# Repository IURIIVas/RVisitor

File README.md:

# RVisitor

Automated robot motion control module

## Description

The module allows to assign the control functions of a wheeled robot to a separate functional unit, reducing the requirements for robot software.   

### Application area
The module provides control of DC motors taking into account information from connected sensors. The module can be used for:
* studying the basic robotic algorithms for controlling the movement of wheeled robots
* research and development of robotic platforms

### Features

* setting and maintaining speed and direction of movement
* identification of obstacles and lack of surface
* wheel odometry
* high current level detection
* configuration save

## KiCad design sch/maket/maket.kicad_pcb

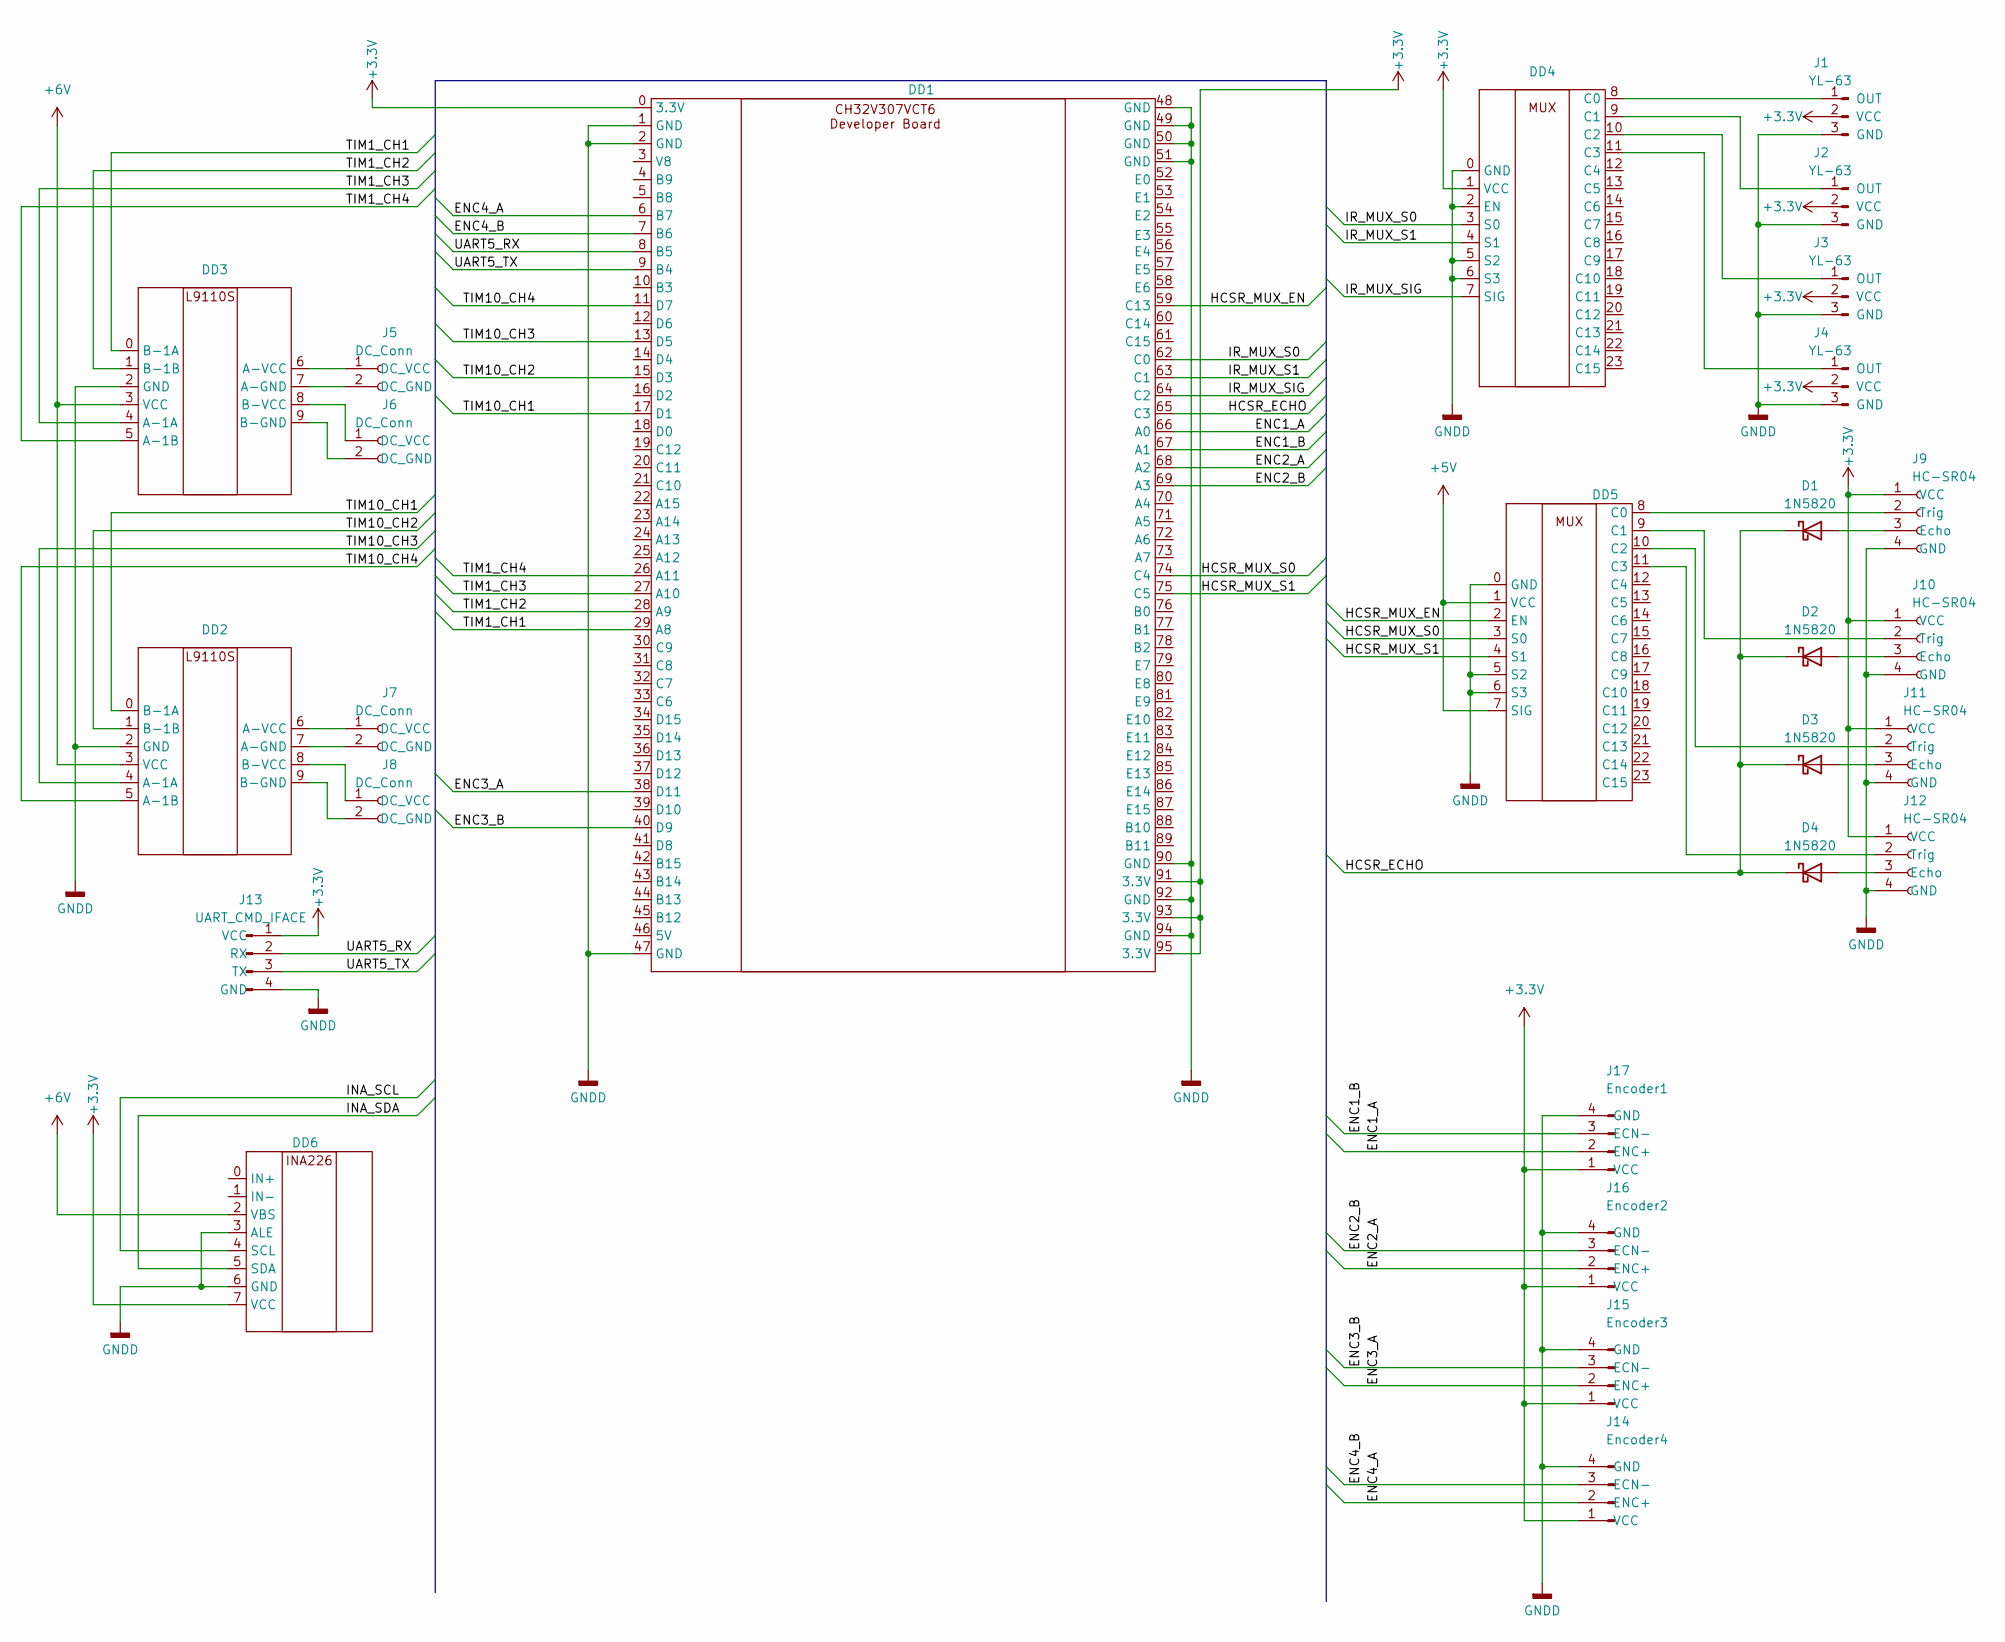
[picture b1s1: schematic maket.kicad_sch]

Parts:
D1, D2, D3, D4: 1N5820; D_DO-201AD_P15.24mm_Horizontal
DD1: CH32V307VCT6 dev board
DD2, DD3: L9110S
DD4, DD5: CD74HC4067_GOOD
DD6: INA226
J1, J2, J3, J4: YL-63; PinHeader_1x03_P2.54mm_Vertical
J5, J6, J7, J8: DC_Conn; JST_PH_S2B-PH-K_1x02_P2.00mm_Horizontal
J9, J10, J11, J12: HC-SR04; PinSocket_1x04_P2.54mm_Vertical
J13: UART_CMD_IFACE; PinSocket_1x04_P2.54mm_Vertical
J14: Encoder4; JST_PH_S4B-PH-K_1x04_P2.00mm_Horizontal
J15: Encoder3; JST_PH_S4B-PH-K_1x04_P2.00mm_Horizontal
J16: Encoder2; JST_PH_S4B-PH-K_1x04_P2.00mm_Horizontal
J17: Encoder1; JST_PH_S4B-PH-K_1x04_P2.00mm_Horizontal

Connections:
+3.3V: DD1.0 (3.3V), DD1.74 (C4), DD1.75 (C5), DD1.91 (3.3V), DD1.93 (3.3V), DD1.95 (3.3V), DD4.1 (VCC), DD5.3 (S0), DD5.4 (S1), DD6.7 (VCC), J1.2 (VCC), J2.2 (VCC), J3.2 (VCC), J4.2 (VCC), J9.1 (VCC), J10.1 (VCC), J11.1 (VCC), J12.1 (VCC), J13.1 (VCC), J14.1 (VCC), J15.1 (VCC), J16.1 (VCC), J17.1 (VCC)
+5V: DD5.1 (VCC), DD5.7 (SIG)
+6V: DD2.3 (VCC), DD3.3 (VCC), DD6.2 (VBS)
/ENC1_A: DD1.66 (A0), J17.2 (ENC+)
/ENC1_B: DD1.67 (A1), J17.3 (ECN-)
/ENC2_A: DD1.68 (A2), J16.2 (ENC+)
/ENC2_B: DD1.69 (A3), J16.3 (ECN-)
/ENC3_A: DD1.38 (D11), J15.2 (ENC+)
/ENC3_B: DD1.40 (D9), J15.3 (ECN-)
/ENC4_A: DD1.6 (B7), J14.2 (ENC+)
/ENC4_B: DD1.7 (B6), J14.3 (ECN-)
/HCSR_ECHO: D1.1 (K), D2.1 (K), D3.1 (K), D4.1 (K), DD1.65 (C3)
/HCSR_MUX_EN: DD1.59 (C13), DD5.2 (EN)
/INA_SCL: DD6.4 (SCL)
/INA_SDA: DD6.5 (SDA)
/IR_MUX_S0: DD1.62 (C0), DD4.3 (S0)
/IR_MUX_S1: DD1.63 (C1), DD4.4 (S1)
/IR_MUX_SIG: DD1.64 (C2), DD4.7 (SIG)
/TIM1_CH1: DD1.29 (A8), DD3.0 (B-1A)
/TIM1_CH2: DD1.28 (A9), DD3.1 (B-1B)
/TIM1_CH3: DD1.27 (A10), DD3.4 (A-1A)
/TIM1_CH4: DD1.26 (A11), DD3.5 (A-1B)
/TIM10_CH1: DD1.17 (D1), DD2.0 (B-1A)
/TIM10_CH2: DD1.15 (D3), DD2.1 (B-1B)
/TIM10_CH3: DD1.13 (D5), DD2.4 (A-1A)
/TIM10_CH4: DD1.11 (D7), DD2.5 (A-1B)
/UART5_RX: DD1.8 (B5), J13.2 (RX)
/UART5_TX: DD1.9 (B4), J13.3 (TX)
GNDD: DD1.1 (GND), DD1.2 (GND), DD1.47 (GND), DD1.48 (GND), DD1.49 (GND), DD1.50 (GND), DD1.51 (GND), DD1.90 (GND), DD1.92 (GND), DD1.94 (GND), DD2.2 (GND), DD3.2 (GND), DD4.0 (GND), DD4.2 (EN), DD4.5 (S2), DD4.6 (S3), DD5.0 (GND), DD5.5 (S2), DD5.6 (S3), DD6.3 (ALE), DD6.6 (GND), J1.3 (GND), J2.3 (GND), J3.3 (GND), J4.3 (GND), J9.4 (GND), J10.4 (GND), J11.4 (GND), J12.4 (GND), J13.4 (GND), J14.4 (GND), J15.4 (GND), J16.4 (GND), J17.4 (GND)
unnamed: D1.2 (A), J9.3 (Echo)
unnamed: D2.2 (A), J10.3 (Echo)
unnamed: D3.2 (A), J11.3 (Echo)
unnamed: D4.2 (A), J12.3 (Echo)
unnamed: DD2.7 (A-GND), J7.2 (DC_GND)
unnamed: DD2.6 (A-VCC), J7.1 (DC_VCC)
unnamed: DD2.9 (B-GND), J8.2 (DC_GND)
unnamed: DD2.8 (B-VCC), J8.1 (DC_VCC)
unnamed: DD3.7 (A-GND), J5.2 (DC_GND)
unnamed: DD3.6 (A-VCC), J5.1 (DC_VCC)
unnamed: DD3.9 (B-GND), J6.2 (DC_GND)
unnamed: DD3.8 (B-VCC), J6.1 (DC_VCC)
unnamed: DD4.8 (C0), J1.1 (OUT)
unnamed: DD4.9 (C1), J2.1 (OUT)
unnamed: DD4.10 (C2), J3.1 (OUT)
unnamed: DD4.11 (C3), J4.1 (OUT)
unnamed: DD5.8 (C0), J9.2 (Trig)
unnamed: DD5.9 (C1), J10.2 (Trig)
unnamed: DD5.10 (C2), J11.2 (Trig)
unnamed: DD5.11 (C3), J12.2 (Trig)

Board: 2 copper layers, 27 parts (0 on the bottom side), 47 nets, no tracks yet.

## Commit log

2023-10-18 Initial commit. Blink LEDs Function
2023-10-21 Command Interface on USART2. print Hello World and unknown command added to command interface.
2023-10-22 IR sensor HW-201 init.
2023-11-09 dc motor 0 driver. change direction with cmd interface
2023-11-10 Speed change function added. lib/m_string - added str to int convertion.
2023-11-26 Change USART2 pins to GPIOD. GPIO init function of hw-201 fixed
2023-11-28 HC_SR04 capture started. Added Trig pin functionality with timer and gpio.
2023-11-30 trig pin enable function fixed, 9 timer used to count 10 microseconds
2023-12-01 echo from hc-sr04 get. distance
2023-12-09 hard fault issue
2023-12-11 pid controller develop started.
    - change vTaskDelay from ticks to ms
    - delete blink_led_task
    - convert string to double function added
    - pow function added
2023-12-13 cmd interface sends data in 2 seconds dc_control only by pid, in cmd iface only speed requiered all settings goes to struct tim8 changed to tim10 tim3 changed to tim9 usart2 changed to uart5 defined 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
2023-12-17 function string to double changed tim for dc control changed, from tim8 to tim10 tim3 changes for tim9 hc_sr04 now not working, because of no timer
2023-12-17 working pid
2023-12-17 odometry task. calculate odometry with encoder values dc_motor name added uart_send_double function added
2023-12-17 cmd_params added
2023-12-17 spi flash init
2023-12-21 spi flash driver init
2023-12-21 structs rename dc_motor_controller add
2023-12-24 ina226 i2c lib
2023-12-24 ina226 get current and voltage task
2023-12-25 get current and voltage cmd in command interface
2023-12-26 fixed timer on hc_sr04
2023-12-31 code documentation with doxygen
2024-01-05 dc_motor_driver fixed. brief on hc_sr04_added. i2c wrong tranciever fixed. flags active param added
2024-01-05 testbench configuration. spi flash test
2024-01-05 build config fixed
2024-01-05 defines change
2024-01-10 [debug][motor_controller] => dc_motor_driver task deleted. converted to module and relocated to dc_motor_controller task => odometry task deleted. converted to module and relocated to dc_motor_contro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
2024-01-10 [debug][cmd_interface] => check if written parameters to flash is correct
2024-01-10 [rework] => project structure changed => all soft moved to ./soft folder => doc folder for doxygen generation added => sch folder for schematic added
2024-01-10 [odometry][cmd_iface] => corrected print double function. fixed skipped 0 after dot and double - => odometry threshold added. if left side and right side differs less than 0.001 meter than left_side 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
2024-02-22 [sch] new board add
2024-03-23 [sch] rvisitor_module_board_v1 => power lines added
2024-03-23 [soft] rework => Start reworking vendors lib => GPIO lib reworked => core_riscv reworked
2024-03-23 gpio refactoring start
2024-04-25 little refactor
2024-04-25 maket pcb start. maket add footprints. module_board_v1 start
2024-05-01 PCB module. readme update
2024-07-28 new chapter
2024-08-02 missing files
2024-08-04 dc motor controller with pid working mode
2024-08-04 cmd iface return
2024-09-08 encoders and dc motor map new maket board implemented
2024-11-13 Removed project dirs
2024-11-13 Added makefile for non IDE
2024-11-13 Scripts and doc folder added in project root
2024-11-14 Angular speed to RPM speed conversion
